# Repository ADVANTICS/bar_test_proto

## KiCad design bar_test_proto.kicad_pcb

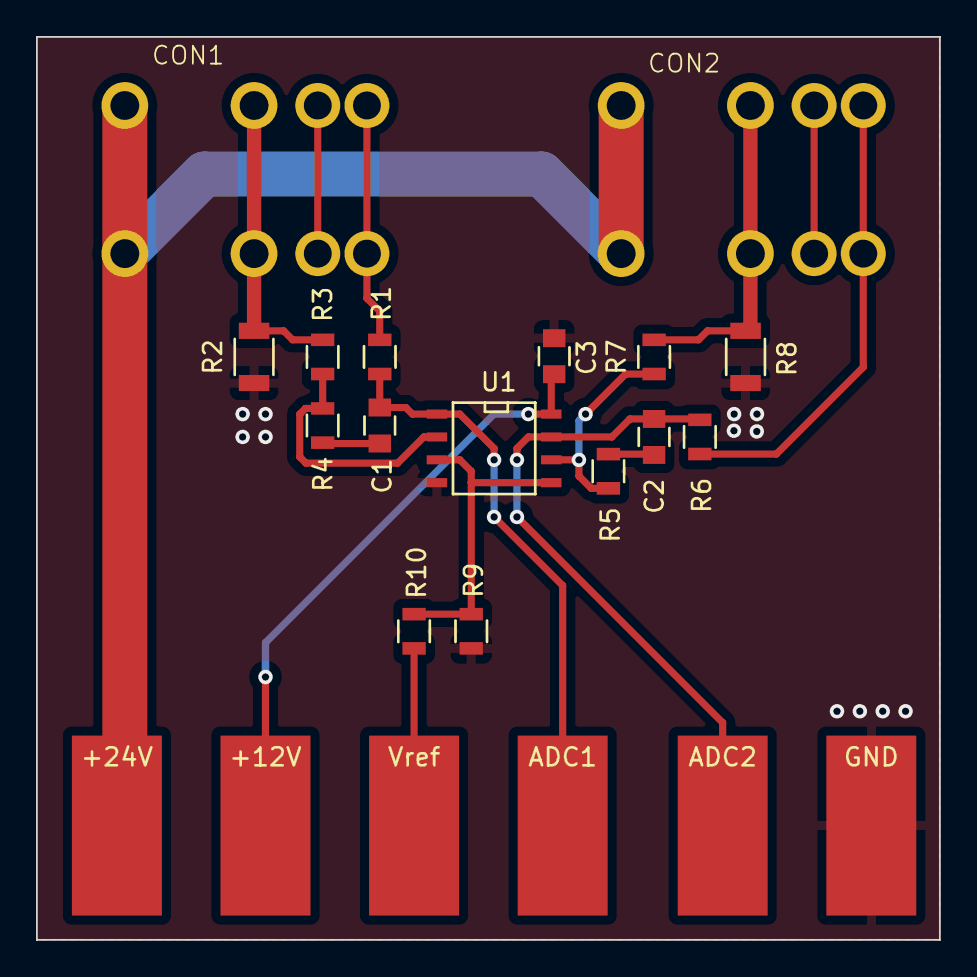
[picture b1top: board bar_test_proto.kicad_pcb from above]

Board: 2 copper layers, 50.2 x 50.2 mm, 22 parts (0 on the bottom side), 15 nets.

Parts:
+12V: +12V; SolderWirePad_single_SMD_5x10mm
+24V: +24V; SolderWirePad_single_SMD_5x10mm
ADC1: ADC1; SolderWirePad_single_SMD_5x10mm
ADC2: ADC2; SolderWirePad_single_SMD_5x10mm
C1, C2: 1n; C_0805
C3: 1u; C_0805
CON1, CON2: T4PNF-L214-ST-xx
GND: GND; SolderWirePad_single_SMD_5x10mm
R1, R6: 100; R_0805
R2, R8: 100m; R_1206
R3, R4, R5, R7, R10: 10k; R_0805
R9: 2k2; R_0805
U1: OPA1678; SOIC-8-N
Vref: Vref; SolderWirePad_single_SMD_5x10mm

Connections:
+12V0: +12V.1, C3.1 (A), U1.8 (V+)
+24V: +24V.1, CON1.1 (D), CON2.1 (D)
ADC1: ADC1.1, C1.2 (K), R1.1, U1.1
ADC2: ADC2.1, C2.2 (K), R6.1, U1.7
GND: C3.2 (K), GND.1, R2.1, R8.1, R9.1, U1.4 (V-)
unnamed: C1.1 (A), R4.2
unnamed: C2.1 (A), R5.2
unnamed: CON1.4 (G), R1.2
unnamed: CON1.2 (S), R2.2, R3.2
unnamed: CON2.4 (G), R6.2
unnamed: CON2.2 (S), R7.2, R8.2
unnamed: R9.2, R10.1, U1.3 (+), U1.5 (+)
unnamed: R3.1, R4.1, U1.2 (-)
unnamed: R5.1, R7.1, U1.6 (-)
Vref: R10.2, Vref.1

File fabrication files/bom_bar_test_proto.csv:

Comment,Designator,Footprint,JLC part
10k,"R7,R10,R3,R4,R5",R_0805,C17414
2k2,R9,R_0805,C17520
100,"R6,R1",R_0805,C17408
1u,C3,C_0805,C215803
1n,"C2,C1",C_0805,C46553
100m,"R2,R8",R_1206,C2903496
OPA1678,U1,SOIC-8-N,C192421

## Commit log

2024-02-22 Closed files
2024-02-26 Added simple PCB layout
2024-02-26 2.5 mm line for 24V
2024-03-11 Added decoupling cap 1u
2024-03-13 fabrication files are added
